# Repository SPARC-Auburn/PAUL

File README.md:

# PAUL
Phased Array Ultrasonic Levitator

TODO

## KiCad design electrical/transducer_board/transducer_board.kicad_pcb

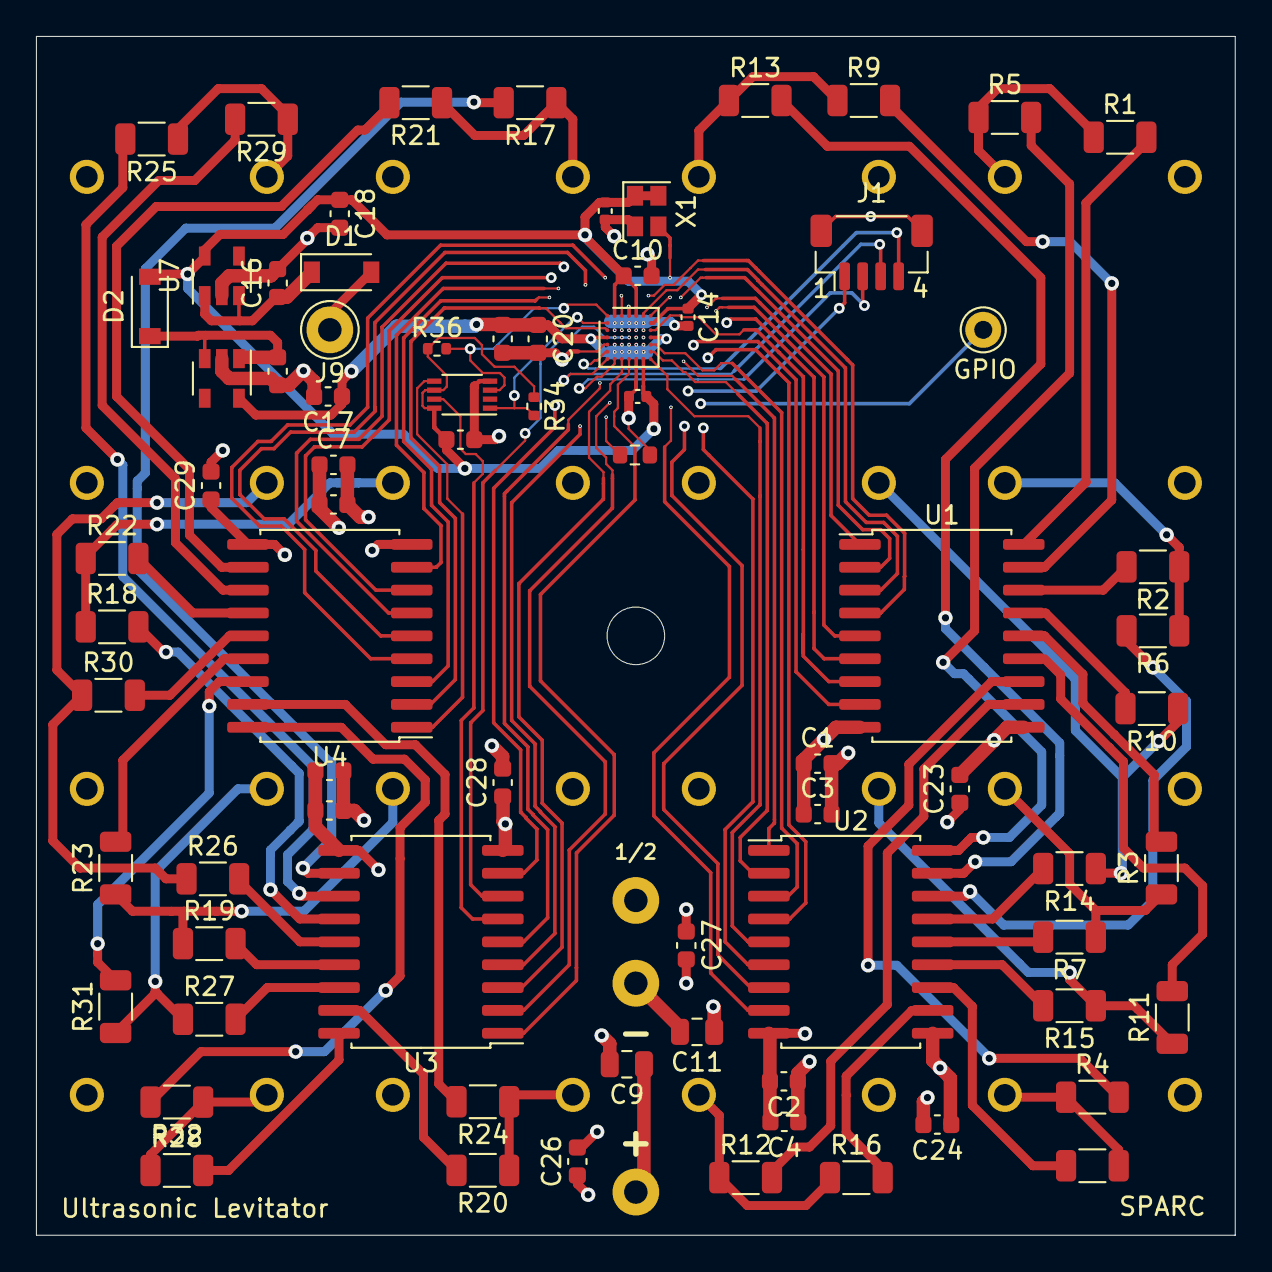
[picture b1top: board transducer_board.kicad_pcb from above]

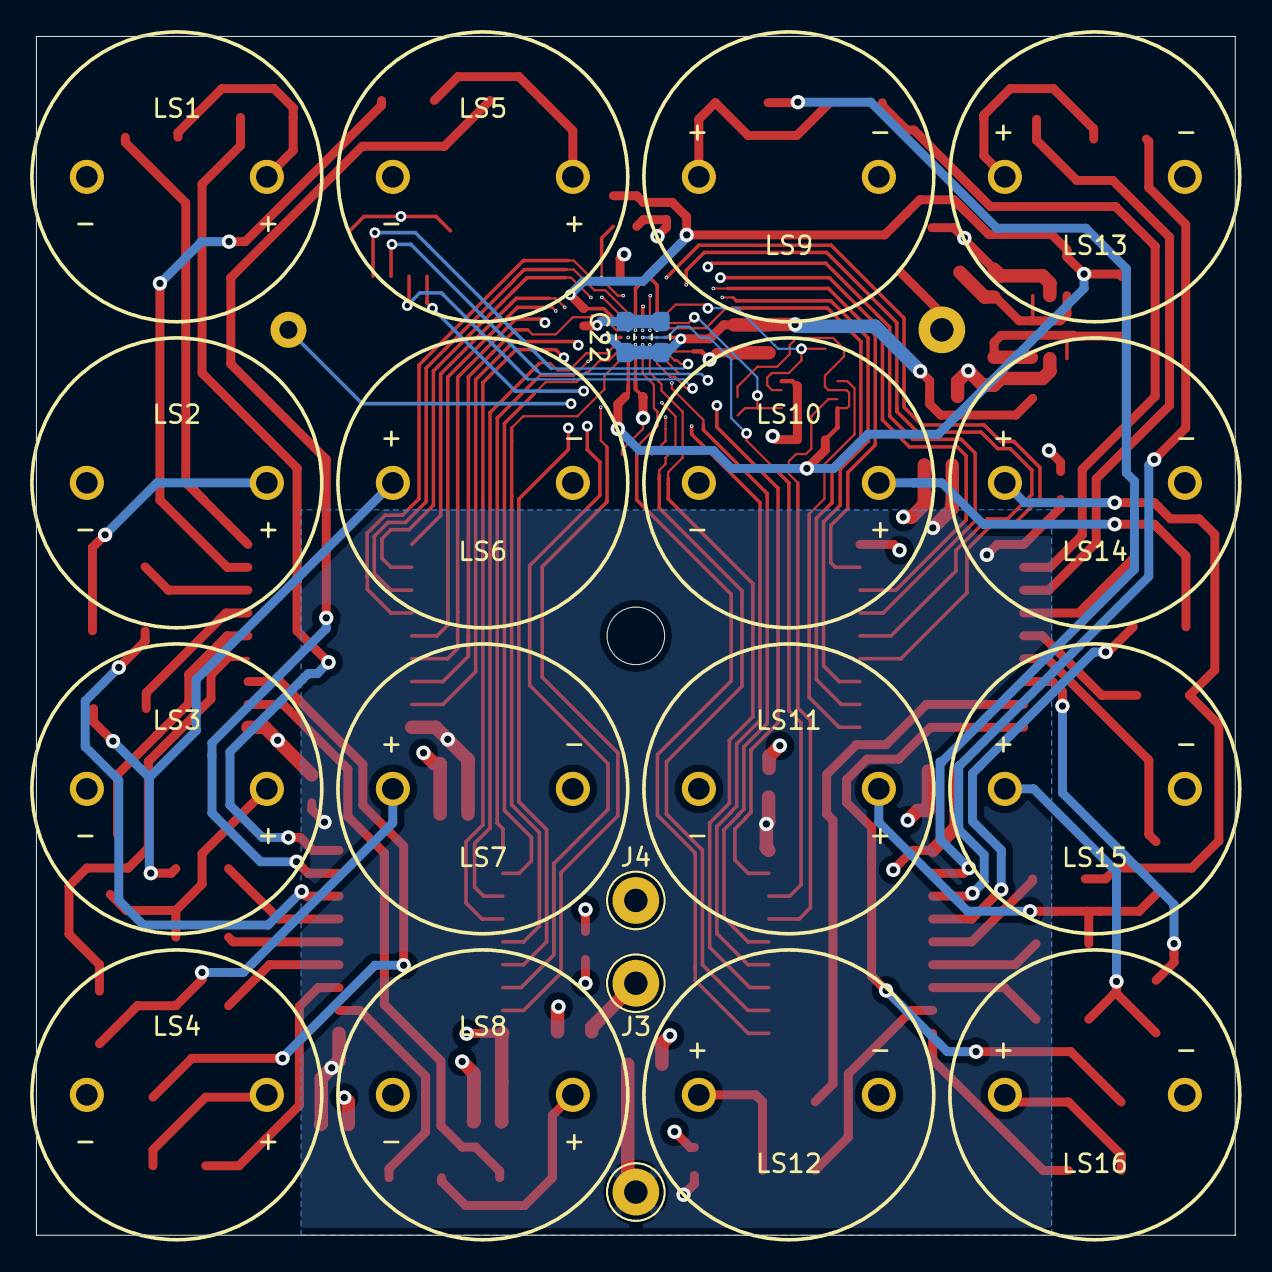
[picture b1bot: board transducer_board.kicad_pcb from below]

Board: 4 copper layers, 66.6 x 66.6 mm, 97 parts (21 on the bottom side), 97 nets.

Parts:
C1, C2, C5, C6, C10, C13, C20, C23, C24, C26, C27, C28, C29: 100nF; C_0603_1608Metric
C3, C4, C7, C8, C15, C16, C17, C18, C19: 1uF; C_0603_1608Metric
C9, C11: 10uF; C_0805_2012Metric
C12, C14, C25: 10nF; C_0402_1005Metric
C21: 10nF; C_0603_1608Metric_Pad1.08x0.95mm_HandSolder
C22: 1nF; C_0603_1608Metric_Pad1.08x0.95mm_HandSolder
D1, D2: D; D_SOD-123
J1: Conn_01x04_MountingPin; JST_SH_BM04B-SRSS-TB_1x04-1MP_P1.00mm_Vertical
J2, J3, J4, J9: Conn_01x01; Pin_D1.3mm_L11.0mm
J6: Conn_01x01; Pin_D1.0mm_L10.0mm
LS1, LS2, LS3, LS4, LS5, LS6, LS7, LS8, LS9, LS10, LS11, LS12, LS13, LS14, LS15, LS16: Speaker_Ultrasound; Ultrasonic_Transducer_T40-16
R1, R2, R3, R4, R5, R6, R7, R8, R9, R10, R11, R12, R13, R14, R15, R16, R17, R18, R19, R20, R21, R22, R23, R24, R25, R26, R27, R28, R29, R30, R31, R32: 47; R_1206_3216Metric
R33: 10k; R_0603_1608Metric
R34, R36: 4.7k; R_0402_1005Metric
U1, U3: XL62783; SOIC-18W_7.5x11.6mm_P1.27mm_Weird
U2, U4: XL62083; SOIC-18W_7.5x11.6mm_P1.27mm_Weird
U5: LCMXO3L-2100E-5UWG49; ST_WLCSP-49_Die433
U6: ME6211C12M5G-N; SOT-23-5
U7: PJ9193M33SE; SOT-23-5
U8: 74LVC3G34; VSSOP-8_2.3x2mm_P0.5mm
X1: X1G004171001600; Oscillator_SMD_SeikoEpson_SG210-4Pin_2.5x2.0mm

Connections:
/CLK: U5.A7 (PL2A_L_GPLLT_IN), X1.3 (OUT)
/GPIO_1: J6.1, U5.F5 (PB8B_SO_SPISO)
/JTAGENB: R33.1, U5.F2 (PT20C_JTAGENB)
/SCK: J1.1, U5.F6 (PB8A_MCLK_CCLK)
/SPI_SI: J1.3, U5.G1 (PB25B_SI_SISPI)
/SPI_SS: J1.2, U5.G2 (PB25A_SN)
/SYNC: J1.4, U5.F1 (PT20D_PROGRAMN)
/T1+: U1.1 (I1), U5.B6 (PL2B_L_GPLLC_IN)
/T1-: U2.1 (I1), U5.E6 (PL5A)
/T2+: U1.3 (I3), U5.A6 (PT12C_TDO)
/T2-: U2.3 (I3), U5.E7 (PB3A)
/T3+: U1.5 (I5), U5.C6 (PL3B_PCLKC5_0)
/T3-: U2.5 (I5), U5.G7 (PB5A_CSSPIN)
/T4+: U1.7 (I7), U5.C7 (PL3A_PCLKT5_0)
/T4-: U2.7 (I7), U5.E3 (PB11B_PCLKC2_0)
/T5+: U1.2 (I2), U5.B5 (PT16D_TMS)
/T5-: U2.2 (I2), U5.F7 (PB3B)
/T6+: U1.4 (I4), U5.B4 (PT16C_TCK)
/T6-: U2.4 (I4), U5.E5 (PL5B)
/T7+: U1.6 (I6), U5.C5 (PT12D_TDI)
/T7-: U2.6 (I6), U5.E4 (PB11A_PCLKT2_0)
/T8+: U1.8 (I8), U5.D5 (PT10A)
/T8-: U2.8 (I8), U5.F4 (PB12A)
/T9+: U3.8 (I8), U5.D3 (PT17B_PCLKC0_1)
/T9-: U4.8 (I8), U5.B2 (PT20B)
/T10+: U3.6 (I6), U8.7
/T10+_OD: R34.2, U5.B1 (PT24C_INITN), U8.1
/T10-: U4.6 (I6), U5.C4 (PT17A_PCKLT0_1)
/T11+: U3.4 (I4), U5.E2 (PT23A)
/T11-: U4.4 (I4), U5.A3 (PT20A)
/T12+: U3.2 (I2), U5.F3 (PB12B)
/T12-: U4.2 (I2), U5.C1 (PT24A)
/T13+: U3.7 (I7), U5.D4 (PT10B)
/T13-: U4.7 (I7), U5.C3 (PT18D_SDA_PCLKC0_0)
/T14+: U3.5 (I5), U5.D2 (PT24B)
/T14-: U4.5 (I5), U5.B3 (PT18C_SCL_PCLKT0_0)
/T15+: U3.3 (I3), U5.G3 (PB16B_PCLKC2_1)
/T15-: U4.3 (I3), U5.C2 (PT23B)
/T16+: U3.1 (I1), U5.G4 (PB16A_PCLKT2_1)
/T16-: U4.1 (I1), U8.5
/T16-_OD: R36.2, U5.A1 (PT24D_DONE), U8.3
/VMID: C1.2, C2.1, C3.2, C4.1, C5.2, C6.1, C7.2, C8.1, C9.2, C11.1, C26.2, C27.1, J4.1, LS1.2, LS2.2, LS3.2, LS4.2, LS5.2, LS6.2, LS7.2, LS8.2, LS9.2, LS10.2, LS11.2, LS12.2, LS13.2, LS14.2, LS15.2, LS16.2
/V_1.2: C17.1, C19.1, C20.1, C21.1, C22.1, U5.D1 (VCC), U5.D7 (VCC), U6.5 (VOUT)
/V_3.3: C10.1, C12.1, C13.1, C14.1, C18.1, C25.1, D2.2 (A), R34.1, R36.1, U5.A2 (VCCIO0), U5.A5 (VCCIO0), U5.B7 (VCCIO5), U5.G6 (VCCIO2), U7.5 (VOUT), U8.6, U8.8, X1.1 (EN), X1.4 (Vdd)
/V_3.3_D: C15.1, D2.1 (K), U6.1 (VIN), U6.3 (EN)
/V_5: D1.2 (A), J9.1
/V_5_D: C16.1, D1.1 (K), U7.1 (VIN), U7.3 (EN)
GND: C2.2, C4.2, C6.2, C8.2, C10.2, C11.2, C12.2, C13.2, C14.2, C15.2, C16.2, C17.2, C18.2, C19.2, C20.2, C21.2, C22.2, C23.2, C24.2, C25.2, C27.2, C28.2, C29.2, J1.MP (MountPin), J3.1, R33.2, U1.10 (GND), U2.9 (GND), U3.10 (GND), U4.9 (GND), U5.A4 (GND), U5.D6 (GND), U5.E1 (GND), U5.G5 (GND), U6.2 (GND), U7.2 (GND), U8.4, X1.2 (GND)
unnamed: LS1.1, R1.1, R5.1
unnamed: LS2.1, R2.1, R6.1
unnamed: LS3.1, R3.1, R7.1
unnamed: LS4.1, R4.1, R8.1
unnamed: LS5.1, R9.1, R13.1
unnamed: LS6.1, R10.1, R14.1
unnamed: LS7.1, R11.1, R15.1
unnamed: LS8.1, R12.1, R16.1
unnamed: LS9.1, R17.1, R21.1
unnamed: LS10.1, R18.1, R22.1
unnamed: LS11.1, R19.1, R23.1
unnamed: LS12.1, R20.1, R24.1
unnamed: LS13.1, R25.1, R29.1
unnamed: LS14.1, R26.1, R30.1
unnamed: LS15.1, R27.1, R31.1
unnamed: LS16.1, R28.1, R32.1
unnamed: R1.2, U1.18 (O1)
unnamed: R2.2, U1.16 (O3)
unnamed: R3.2, U1.14 (O5)
unnamed: R4.2, U1.12 (O7)
unnamed: R5.2, U2.18 (O1)
unnamed: R6.2, U2.16 (O3)
unnamed: R7.2, U2.14 (O5)
unnamed: R8.2, U2.12 (O7)
unnamed: R9.2, U1.17 (O2)
unnamed: R10.2, U1.15 (O4)
unnamed: R11.2, U1.13 (O6)
unnamed: R12.2, U1.11 (O8)
unnamed: R13.2, U2.17 (O2)
unnamed: R14.2, U2.15 (O4)
unnamed: R15.2, U2.13 (O6)
unnamed: R16.2, U2.11 (O8)
unnamed: R17.2, U3.11 (O8)
unnamed: R18.2, U3.13 (O6)
unnamed: R19.2, U3.15 (O4)
unnamed: R20.2, U3.17 (O2)
unnamed: R21.2, U4.11 (O8)
unnamed: R22.2, U4.13 (O6)
unnamed: R23.2, U4.15 (O4)
unnamed: R24.2, U4.17 (O2)
unnamed: R25.2, U3.12 (O7)
unnamed: R26.2, U3.14 (O5)
unnamed: R27.2, U3.16 (O3)
unnamed: R28.2, U3.18 (O1)
unnamed: R29.2, U4.12 (O7)
unnamed: R30.2, U4.14 (O5)
unnamed: R31.2, U4.16 (O3)
unnamed: R32.2, U4.18 (O1)
VCC: C1.1, C3.1, C5.1, C7.1, C9.1, C23.1, C24.1, C26.1, C28.1, C29.1, J2.1, U1.9 (Vcc), U2.10 (Vcc), U3.9 (Vcc), U4.10 (Vcc)

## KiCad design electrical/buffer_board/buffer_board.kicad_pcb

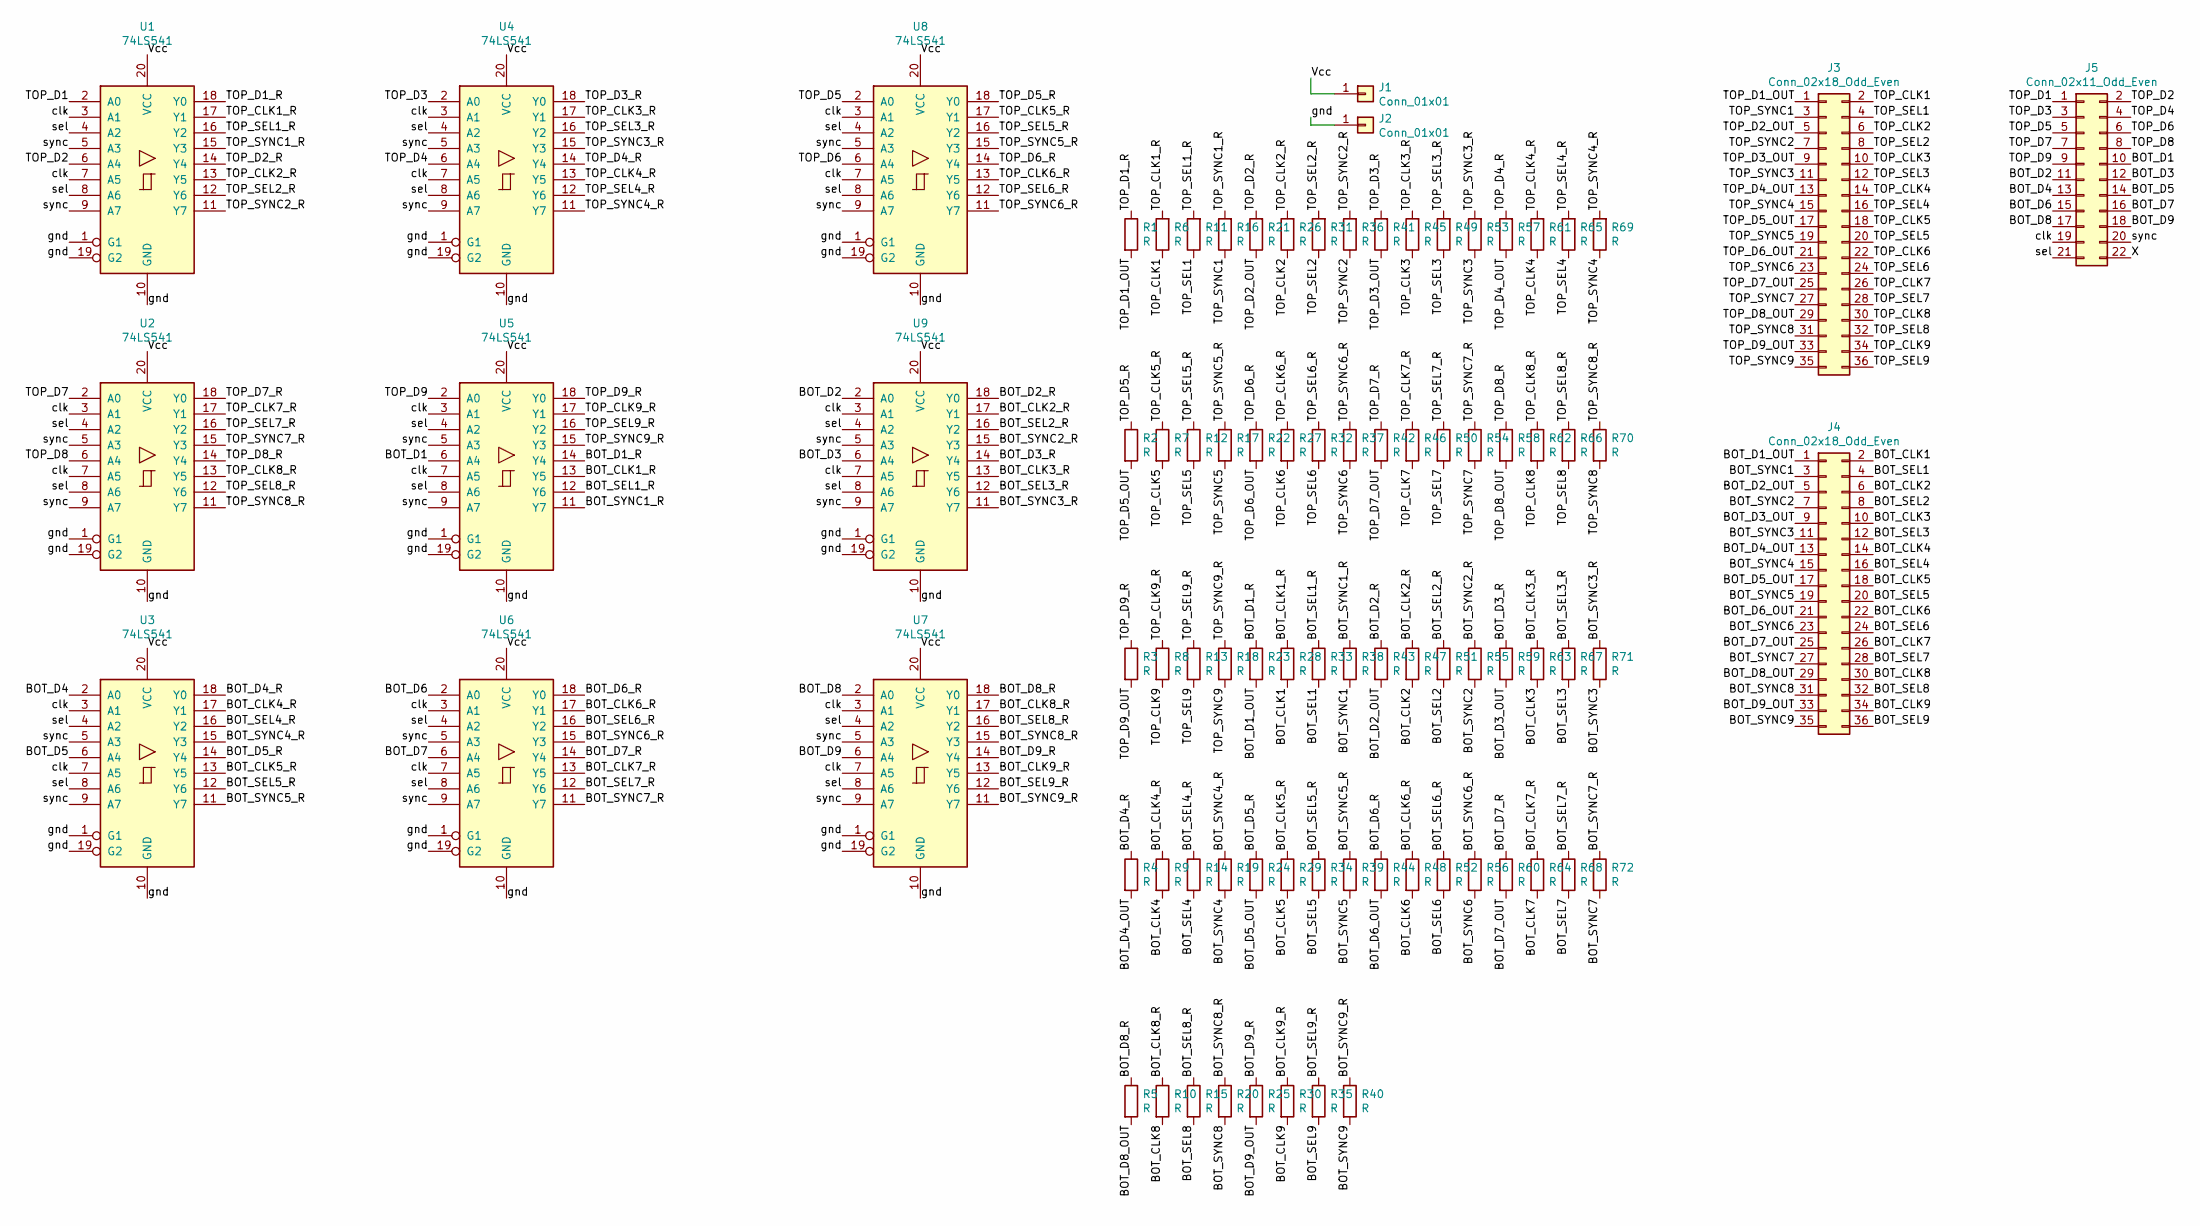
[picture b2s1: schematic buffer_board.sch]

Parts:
J1, J2: Conn_01x01; Pin_D1.3mm_L11.0mm
J3, J4: Conn_02x18_Odd_Even; PinSocket_2x18_P2.54mm_Vertical
J5: Conn_02x11_Odd_Even; PinSocket_2x11_P2.54mm_Vertical
R1, R2, R3, R4, R5, R6, R7, R8, R9, R10, R11, R12, R13, R14, R15, R16, R17, R18, R19, R20, R21, R22, R23, R24, R25, R26, R27, R28, R29, R30, R31, R32, R33, R34, R35, R36, R37, R38, R39, R40, R41, R42, R43, R44, R45, R46, R47, R48, R49, R50, R51, R52, R53, R54, R55, R56, R57, R58, R59, R60, R61, R62, R63, R64, R65, R66, R67, R68, R69, R70, R71, R72: R; R_1206_3216Metric
U1, U2, U3, U4, U5, U6, U7, U8, U9: 74LS541; 74HC541

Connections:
/BOT_CLK1: J4.2, R28.2
/BOT_CLK1_R: R28.1, U5.13 (Y5)
/BOT_CLK2: J4.6, R47.2
/BOT_CLK2_R: R47.1, U9.17 (Y1)
/BOT_CLK3: J4.10, R63.2
/BOT_CLK3_R: R63.1, U9.13 (Y5)
/BOT_CLK4: J4.14, R9.2
/BOT_CLK4_R: R9.1, U3.17 (Y1)
/BOT_CLK5: J4.18, R29.2
/BOT_CLK5_R: R29.1, U3.13 (Y5)
/BOT_CLK6: J4.22, R48.2
/BOT_CLK6_R: R48.1, U6.17 (Y1)
/BOT_CLK7: J4.26, R64.2
/BOT_CLK7_R: R64.1, U6.13 (Y5)
/BOT_CLK8: J4.30, R10.2
/BOT_CLK8_R: R10.1, U7.17 (Y1)
/BOT_CLK9: J4.34, R30.2
/BOT_CLK9_R: R30.1, U7.13 (Y5)
/BOT_D1: J5.10, U5.6 (A4)
/BOT_D1_OUT: J4.1, R23.2
/BOT_D1_R: R23.1, U5.14 (Y4)
/BOT_D2: J5.11, U9.2 (A0)
/BOT_D2_OUT: J4.5, R43.2
/BOT_D2_R: R43.1, U9.18 (Y0)
/BOT_D3: J5.12, U9.6 (A4)
/BOT_D3_OUT: J4.9, R59.2
/BOT_D3_R: R59.1, U9.14 (Y4)
/BOT_D4: J5.13, U3.2 (A0)
/BOT_D4_OUT: J4.13, R4.2
/BOT_D4_R: R4.1, U3.18 (Y0)
/BOT_D5: J5.14, U3.6 (A4)
/BOT_D5_OUT: J4.17, R24.2
/BOT_D5_R: R24.1, U3.14 (Y4)
/BOT_D6: J5.15, U6.2 (A0)
/BOT_D6_OUT: J4.21, R44.2
/BOT_D6_R: R44.1, U6.18 (Y0)
/BOT_D7: J5.16, U6.6 (A4)
/BOT_D7_OUT: J4.25, R60.2
/BOT_D7_R: R60.1, U6.14 (Y4)
/BOT_D8: J5.17, U7.2 (A0)
/BOT_D8_OUT: J4.29, R5.2
/BOT_D8_R: R5.1, U7.18 (Y0)
/BOT_D9: J5.18, U7.6 (A4)
/BOT_D9_OUT: J4.33, R25.2
/BOT_D9_R: R25.1, U7.14 (Y4)
/BOT_SEL1: J4.4, R33.2
/BOT_SEL1_R: R33.1, U5.12 (Y6)
/BOT_SEL2: J4.8, R51.2
/BOT_SEL2_R: R51.1, U9.16 (Y2)
/BOT_SEL3: J4.12, R67.2
/BOT_SEL3_R: R67.1, U9.12 (Y6)
/BOT_SEL4: J4.16, R14.2
/BOT_SEL4_R: R14.1, U3.16 (Y2)
/BOT_SEL5: J4.20, R34.2
/BOT_SEL5_R: R34.1, U3.12 (Y6)
/BOT_SEL6: J4.24, R52.2
/BOT_SEL6_R: R52.1, U6.16 (Y2)
/BOT_SEL7: J4.28, R68.2
/BOT_SEL7_R: R68.1, U6.12 (Y6)
/BOT_SEL8: J4.32, R15.2
/BOT_SEL8_R: R15.1, U7.16 (Y2)
/BOT_SEL9: J4.36, R35.2
/BOT_SEL9_R: R35.1, U7.12 (Y6)
/BOT_SYNC1: J4.3, R38.2
/BOT_SYNC1_R: R38.1, U5.11 (Y7)
/BOT_SYNC2: J4.7, R55.2
/BOT_SYNC2_R: R55.1, U9.15 (Y3)
/BOT_SYNC3: J4.11, R71.2
/BOT_SYNC3_R: R71.1, U9.11 (Y7)
/BOT_SYNC4: J4.15, R19.2
/BOT_SYNC4_R: R19.1, U3.15 (Y3)
/BOT_SYNC5: J4.19, R39.2
/BOT_SYNC5_R: R39.1, U3.11 (Y7)
/BOT_SYNC6: J4.23, R56.2
/BOT_SYNC6_R: R56.1, U6.15 (Y3)
/BOT_SYNC7: J4.27, R72.2
/BOT_SYNC7_R: R72.1, U6.11 (Y7)
/BOT_SYNC8: J4.31, R20.2
/BOT_SYNC8_R: R20.1, U7.15 (Y3)
/BOT_SYNC9: J4.35, R40.2
/BOT_SYNC9_R: R40.1, U7.11 (Y7)
/TOP_CLK1: J3.2, R6.1
/TOP_CLK1_R: R6.2, U1.17 (Y1)
/TOP_CLK2: J3.6, R26.1
/TOP_CLK2_R: R26.2, U1.13 (Y5)
/TOP_CLK3: J3.10, R45.1
/TOP_CLK3_R: R45.2, U4.17 (Y1)
/TOP_CLK4: J3.14, R61.1
/TOP_CLK4_R: R61.2, U4.13 (Y5)
/TOP_CLK5: J3.18, R7.2
/TOP_CLK5_R: R7.1, U8.17 (Y1)
/TOP_CLK6: J3.22, R27.2
/TOP_CLK6_R: R27.1, U8.13 (Y5)
/TOP_CLK7: J3.26, R46.2
/TOP_CLK7_R: R46.1, U2.17 (Y1)
/TOP_CLK8: J3.30, R62.2
/TOP_CLK8_R: R62.1, U2.13 (Y5)
/TOP_CLK9: J3.34, R8.2
/TOP_CLK9_R: R8.1, U5.17 (Y1)
/TOP_D1: J5.1, U1.2 (A0)
/TOP_D1_OUT: J3.1, R1.2
/TOP_D1_R: R1.1, U1.18 (Y0)
/TOP_D2: J5.2, U1.6 (A4)
/TOP_D2_OUT: J3.5, R21.1
/TOP_D2_R: R21.2, U1.14 (Y4)
/TOP_D3: J5.3, U4.2 (A0)
/TOP_D3_OUT: J3.9, R41.1
/TOP_D3_R: R41.2, U4.18 (Y0)
/TOP_D4: J5.4, U4.6 (A4)
/TOP_D4_OUT: J3.13, R57.1
/TOP_D4_R: R57.2, U4.14 (Y4)
/TOP_D5: J5.5, U8.2 (A0)
/TOP_D5_OUT: J3.17, R2.2
/TOP_D5_R: R2.1, U8.18 (Y0)
/TOP_D6: J5.6, U8.6 (A4)
/TOP_D6_OUT: J3.21, R22.2
/TOP_D6_R: R22.1, U8.14 (Y4)
/TOP_D7: J5.7, U2.2 (A0)
/TOP_D7_OUT: J3.25, R42.2
/TOP_D7_R: R42.1, U2.18 (Y0)
/TOP_D8: J5.8, U2.6 (A4)
/TOP_D8_OUT: J3.29, R58.2
/TOP_D8_R: R58.1, U2.14 (Y4)
/TOP_D9: J5.9, U5.2 (A0)
/TOP_D9_OUT: J3.33, R3.2
/TOP_D9_R: R3.1, U5.18 (Y0)
/TOP_SEL1: J3.4, R11.1
/TOP_SEL1_R: R11.2, U1.16 (Y2)
/TOP_SEL2: J3.8, R31.1
/TOP_SEL2_R: R31.2, U1.12 (Y6)
/TOP_SEL3: J3.12, R49.1
/TOP_SEL3_R: R49.2, U4.16 (Y2)
/TOP_SEL4: J3.16, R65.1
/TOP_SEL4_R: R65.2, U4.12 (Y6)
/TOP_SEL5: J3.20, R12.2
/TOP_SEL5_R: R12.1, U8.16 (Y2)
/TOP_SEL6: J3.24, R32.2
/TOP_SEL6_R: R32.1, U8.12 (Y6)
/TOP_SEL7: J3.28, R50.2
/TOP_SEL7_R: R50.1, U2.16 (Y2)
/TOP_SEL8: J3.32, R66.2
/TOP_SEL8_R: R66.1, U2.12 (Y6)
/TOP_SEL9: J3.36, R13.2
/TOP_SEL9_R: R13.1, U5.16 (Y2)
/TOP_SYNC1: J3.3, R16.1
/TOP_SYNC1_R: R16.2, U1.15 (Y3)
/TOP_SYNC2: J3.7, R36.1
/TOP_SYNC2_R: R36.2, U1.11 (Y7)
/TOP_SYNC3: J3.11, R53.1
/TOP_SYNC3_R: R53.2, U4.15 (Y3)
/TOP_SYNC4: J3.15, R69.1
/TOP_SYNC4_R: R69.2, U4.11 (Y7)
/TOP_SYNC5: J3.19, R17.2
/TOP_SYNC5_R: R17.1, U8.15 (Y3)
/TOP_SYNC6: J3.23, R37.2
/TOP_SYNC6_R: R37.1, U8.11 (Y7)
/TOP_SYNC7: J3.27, R54.2
/TOP_SYNC7_R: R54.1, U2.15 (Y3)
/TOP_SYNC8: J3.31, R70.2
/TOP_SYNC8_R: R70.1, U2.11 (Y7)
/TOP_SYNC9: J3.35, R18.2
/TOP_SYNC9_R: R18.1, U5.15 (Y3)
/Vcc: J1.1, U1.20 (VCC), U2.20 (VCC), U3.20 (VCC), U4.20 (VCC), U5.20 (VCC), U6.20 (VCC), U7.20 (VCC), U8.20 (VCC), U9.20 (VCC)
/X: J5.22
/clk: J5.19, U1.3 (A1), U1.7 (A5), U2.3 (A1), U2.7 (A5), U3.3 (A1), U3.7 (A5), U4.3 (A1), U4.7 (A5), U5.3 (A1), U5.7 (A5), U6.3 (A1), U6.7 (A5), U7.3 (A1), U7.7 (A5), U8.3 (A1), U8.7 (A5), U9.3 (A1), U9.7 (A5)
/gnd: J2.1, U1.1 (G1), U1.10 (GND), U1.19 (G2), U2.1 (G1), U2.10 (GND), U2.19 (G2), U3.1 (G1), U3.10 (GND), U3.19 (G2), U4.1 (G1), U4.10 (GND), U4.19 (G2), U5.1 (G1), U5.10 (GND), U5.19 (G2), U6.1 (G1), U6.10 (GND), U6.19 (G2), U7.1 (G1), U7.10 (GND), U7.19 (G2), U8.1 (G1), U8.10 (GND), U8.19 (G2), U9.1 (G1), U9.10 (GND), U9.19 (G2)
/sel: J5.21, U1.4 (A2), U1.8 (A6), U2.4 (A2), U2.8 (A6), U3.4 (A2), U3.8 (A6), U4.4 (A2), U4.8 (A6), U5.4 (A2), U5.8 (A6), U6.4 (A2), U6.8 (A6), U7.4 (A2), U7.8 (A6), U8.4 (A2), U8.8 (A6), U9.4 (A2), U9.8 (A6)
/sync: J5.20, U1.5 (A3), U1.9 (A7), U2.5 (A3), U2.9 (A7), U3.5 (A3), U3.9 (A7), U4.5 (A3), U4.9 (A7), U5.5 (A3), U5.9 (A7), U6.5 (A3), U6.9 (A7), U7.5 (A3), U7.9 (A7), U8.5 (A3), U8.9 (A7), U9.5 (A3), U9.9 (A7)

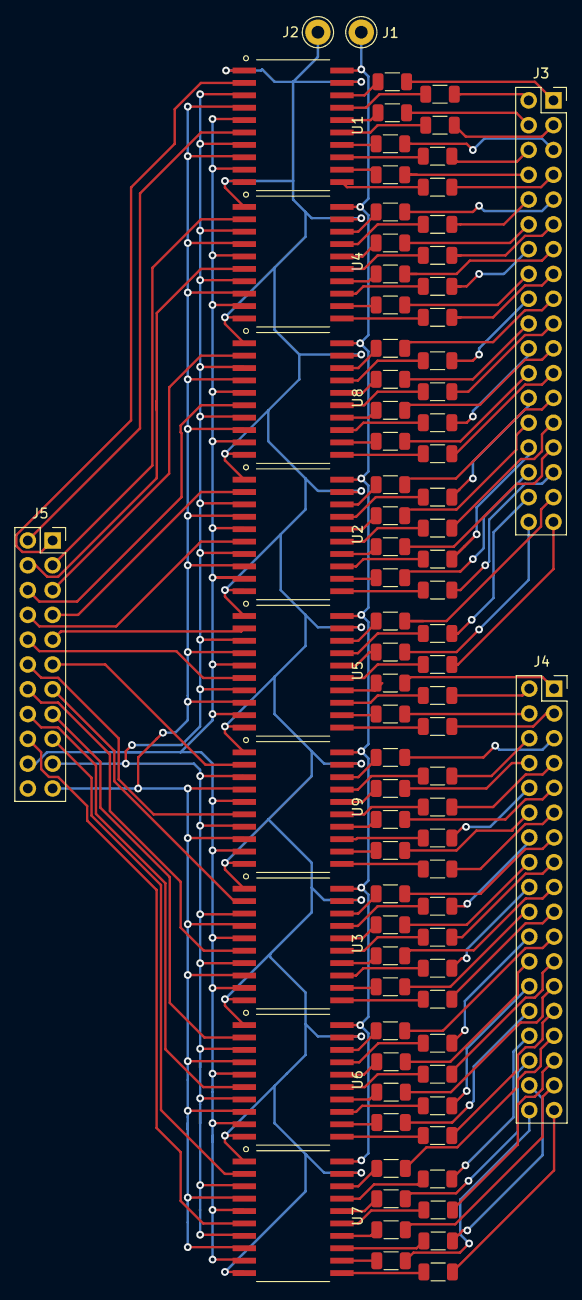
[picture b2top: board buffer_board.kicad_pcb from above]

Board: 2 copper layers, 86 parts (0 on the bottom side), 167 nets.
